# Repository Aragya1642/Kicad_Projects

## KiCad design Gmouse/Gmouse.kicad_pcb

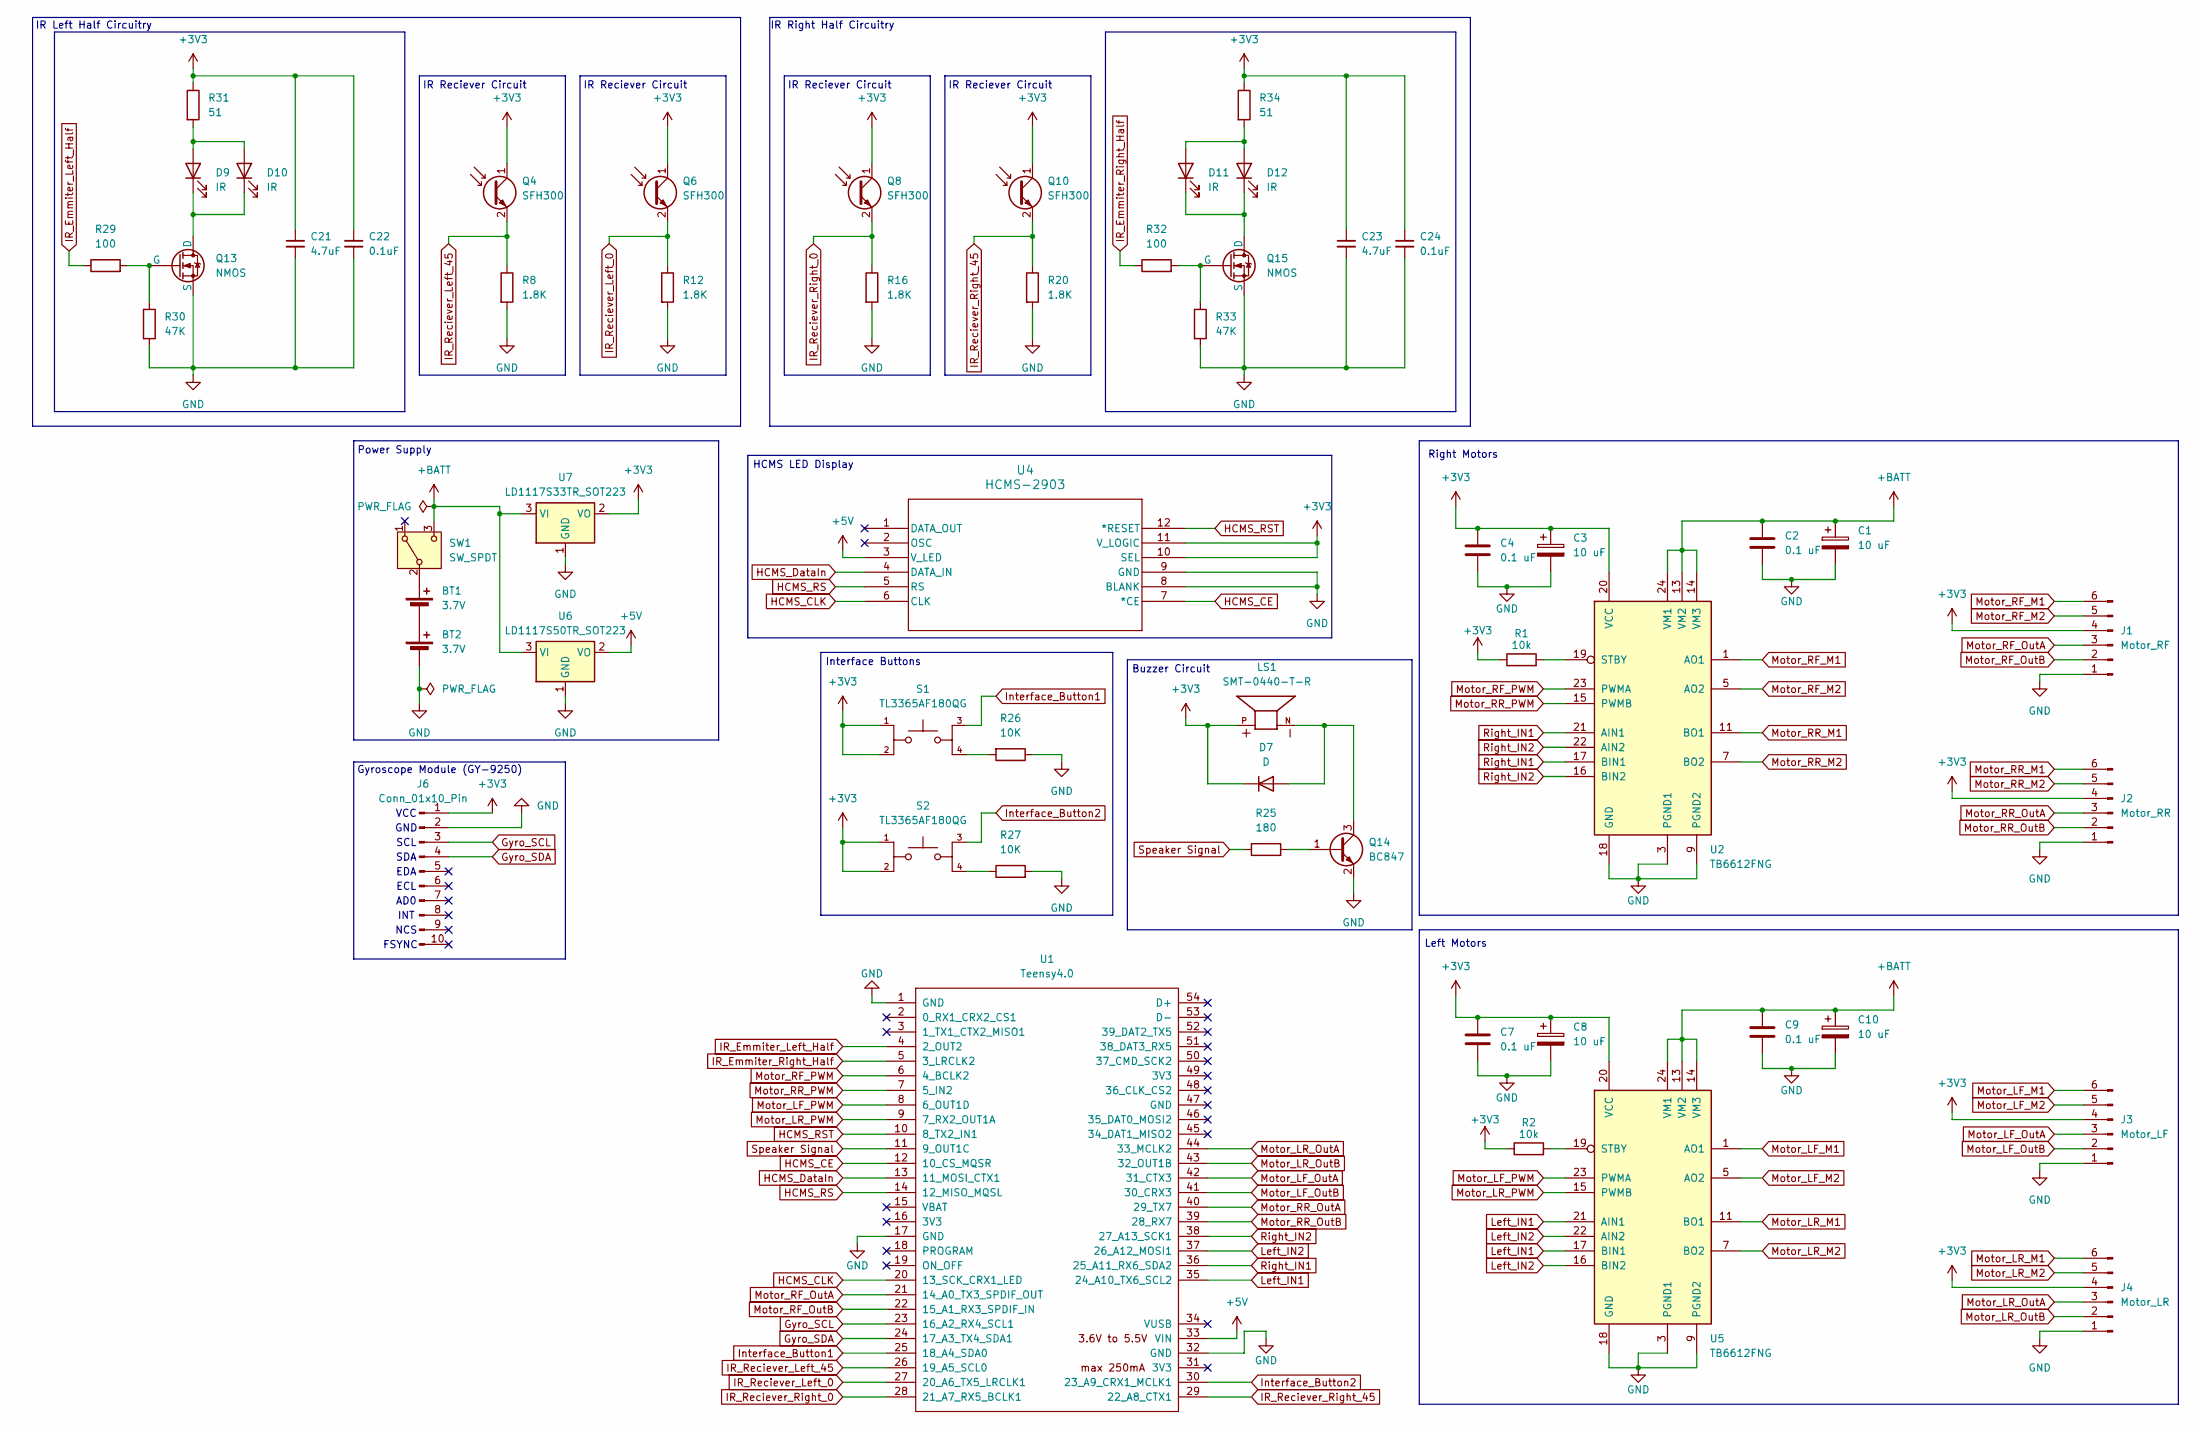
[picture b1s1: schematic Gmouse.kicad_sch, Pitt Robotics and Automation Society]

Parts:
BT1, BT2: 3.7V; JST_PH_B2B-PH-K_1x02_P2.00mm_Vertical
C1, C3, C8, C10: 10 uF; CP_Elec_4x5.4
C2, C4, C7, C9: 0.1 uF; C_1206_3216Metric_Pad1.33x1.80mm_HandSolder
C21, C23: 4.7uF; C_1206_3216Metric_Pad1.33x1.80mm_HandSolder
C22, C24: 0.1uF; C_1206_3216Metric_Pad1.33x1.80mm_HandSolder
D7: D; D_SOD-323_HandSoldering
D9, D10, D11, D12: IR; LED_D5.0mm_Horizontal_O3.81mm_Z9.0mm
J1: Motor_RF; JST_SH_BM06B-SRSS-TB_1x06-1MP_P1.00mm_Vertical
J2: Motor_RR; JST_SH_BM06B-SRSS-TB_1x06-1MP_P1.00mm_Vertical
J3: Motor_LF; JST_SH_BM06B-SRSS-TB_1x06-1MP_P1.00mm_Vertical
J4: Motor_LR; JST_SH_BM06B-SRSS-TB_1x06-1MP_P1.00mm_Vertical
J6: Conn_01x10_Pin; PinHeader_1x10_P2.54mm_Vertical
LS1: SMT-0440-T-R; XDCR_SMT-0440-T-R; PARTREV A
Q4, Q6, Q8, Q10: SFH300; LED_D5.0mm_Horizontal_O1.27mm_Z3.0mm_IRGrey
Q13, Q15: NMOS; SOT-23
Q14: BC847; SOT-23
R1, R2: 10k
R8, R12, R16, R20: 1.8K; R_1206_3216Metric_Pad1.30x1.75mm_HandSolder
R25: 180; R_1206_3216Metric_Pad1.30x1.75mm_HandSolder
R26, R27: 10K; R_1206_3216Metric_Pad1.30x1.75mm_HandSolder
R29, R32: 100; R_1206_3216Metric_Pad1.30x1.75mm_HandSolder
R30, R33: 47K; R_1206_3216Metric_Pad1.30x1.75mm_HandSolder
R31, R34: 51; R_1206_3216Metric_Pad1.30x1.75mm_HandSolder
S1, S2: TL3365AF180QG; SW_TL3365AF180QG; PARTREV A
SW1: SW_SPDT; SW_500SSP1S1M6QEA
U1: Teensy4.0; Teensy40_SMT
U2, U5: TB6612FNG; SSOP-24_5.3x8.2mm_P0.65mm
U4: HCMS-2903; DIP12_HCMS-290X-A_BRA
U6: LD1117S50TR_SOT223; SOT-223-3_TabPin2
U7: LD1117S33TR_SOT223; SOT-223-3_TabPin2

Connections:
+3V3: C3.1, C4.1, C7.1, C8.1, C21.1, C22.1, C23.1, C24.1, D7.1 (K), J1.4, J2.4, J3.4, J4.4, J6.1, LS1.P, Q4.1 (C), Q6.1 (C), Q8.1 (C), Q10.1 (C), R1.1, R2.1, R31.1, R34.1, S1.1, S1.2, S2.1, S2.2, U2.20 (VCC), U4.10 (SEL), U4.11 (V_LOGIC), U5.20 (VCC), U7.2 (VO)
+5V: U1.33 (VIN), U4.3 (V_LED), U6.2 (VO)
+BATT: C1.1, C2.1, C9.1, C10.1, SW1.3 (C), U2.13 (VM2), U2.14 (VM3), U2.24 (VM1), U5.13 (VM2), U5.14 (VM3), U5.24 (VM1), U6.3 (VI), U7.3 (VI)
GND: BT2.2 (-), C1.2, C2.2, C3.2, C4.2, C7.2, C8.2, C9.2, C10.2, C21.2, C22.2, C23.2, C24.2, J1.1, J2.1, J3.1, J4.1, J6.2, Q13.2 (S), Q14.2 (E), Q15.2 (S), R8.2, R12.2, R16.2, R20.2, R26.1, R27.2, R30.2, R33.2, U1.1 (GND), U1.17 (GND), U1.32 (GND), U2.3 (PGND1), U2.4 (PGND1), U2.9 (PGND2), U2.10 (PGND2), U2.18 (GND), U4.8 (BLANK), U4.9 (GND), U5.3 (PGND1), U5.4 (PGND1), U5.9 (PGND2), U5.10 (PGND2), U5.18 (GND), U6.1 (GND), U7.1 (GND)
Gyro_SCL: J6.3, U1.23 (16_A2_RX4_SCL1)
Gyro_SDA: J6.4, U1.24 (17_A3_TX4_SDA1)
HCMS_CE: U1.12 (10_CS_MQSR), U4.7 (*CE)
HCMS_CLK: U1.20 (13_SCK_CRX1_LED), U4.6 (CLK)
HCMS_DataIn: U1.13 (11_MOSI_CTX1), U4.4 (DATA_IN)
HCMS_RS: U1.14 (12_MISO_MQSL), U4.5 (RS)
HCMS_RST: U1.10 (8_TX2_IN1), U4.12 (*RESET)
IR_Emmiter_Left_Half: R29.1, U1.4 (2_OUT2)
IR_Emmiter_Right_Half: R32.1, U1.5 (3_LRCLK2)
IR_Reciever_Left_0: Q6.2 (E), R12.1, U1.27 (20_A6_TX5_LRCLK1)
IR_Reciever_Left_45: Q4.2 (E), R8.1, U1.26 (19_A5_SCL0)
IR_Reciever_Right_0: Q8.2 (E), R16.1, U1.28 (21_A7_RX5_BCLK1)
IR_Reciever_Right_45: Q10.2 (E), R20.1, U1.29 (22_A8_CTX1)
Interface_Button1: S1.3, U1.25 (18_A4_SDA0)
Interface_Button2: S2.3, U1.30 (23_A9_CRX1_MCLK1)
Left_IN1: U1.35 (24_A10_TX6_SCL2), U5.17 (BIN1), U5.21 (AIN1)
Left_IN2: U1.37 (26_A12_MOSI1), U5.16 (BIN2), U5.22 (AIN2)
Motor_LF_M1: J3.6, U5.1 (AO1), U5.2 (AO1)
Motor_LF_M2: J3.5, U5.5 (AO2), U5.6 (AO2)
Motor_LF_OutA: J3.3, U1.42 (31_CTX3)
Motor_LF_OutB: J3.2, U1.41 (30_CRX3)
Motor_LF_PWM: U1.8 (6_OUT1D), U5.23 (PWMA)
Motor_LR_M1: J4.6, U5.11 (BO1), U5.12 (BO1)
Motor_LR_M2: J4.5, U5.7 (BO2), U5.8 (BO2)
Motor_LR_OutA: J4.3, U1.44 (33_MCLK2)
Motor_LR_OutB: J4.2, U1.43 (32_OUT1B)
Motor_LR_PWM: U1.9 (7_RX2_OUT1A), U5.15 (PWMB)
Motor_RF_M1: J1.6, U2.1 (AO1), U2.2 (AO1)
Motor_RF_M2: J1.5, U2.5 (AO2), U2.6 (AO2)
Motor_RF_OutA: J1.3, U1.21 (14_A0_TX3_SPDIF_OUT)
Motor_RF_OutB: J1.2, U1.22 (15_A1_RX3_SPDIF_IN)
Motor_RF_PWM: U1.6 (4_BCLK2), U2.23 (PWMA)
Motor_RR_M1: J2.6, U2.11 (BO1), U2.12 (BO1)
Motor_RR_M2: J2.5, U2.7 (BO2), U2.8 (BO2)
Motor_RR_OutA: J2.3, U1.40 (29_TX7)
Motor_RR_OutB: J2.2, U1.39 (28_RX7)
Motor_RR_PWM: U1.7 (5_IN2), U2.15 (PWMB)
unnamed: BT1.1 (+), SW1.2 (B)
unnamed: BT1.2 (-), BT2.1 (+)
unnamed: D7.2 (A), LS1.N, Q14.3 (C)
unnamed: D9.2 (A), D10.2 (A), R31.2
unnamed: D9.1 (K), D10.1 (K), Q13.3 (D)
unnamed: D11.2 (A), D12.2 (A), R34.2
unnamed: D11.1 (K), D12.1 (K), Q15.3 (D)
unnamed: Q13.1 (G), R29.2, R30.1
unnamed: Q14.1 (B), R25.2
unnamed: Q15.1 (G), R32.2, R33.1
unnamed: R1.2, U2.19 (STBY)
unnamed: R2.2, U5.19 (STBY)
unnamed: R26.2, S1.4
unnamed: R27.1, S2.4
Right_IN1: U1.36 (25_A11_RX6_SDA2), U2.17 (BIN1), U2.21 (AIN1)
Right_IN2: U1.38 (27_A13_SCK1), U2.16 (BIN2), U2.22 (AIN2)
Speaker Signal: R25.1, U1.11 (9_OUT1C)

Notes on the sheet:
Left Motors
Right Motors
EDA
Power Supply
Buzzer Circuit
ECL
GND
NCS
VCC
IR Left Half Circuitry
SDA
FSYNC
INT
IR Right Half Circuitry
HCMS LED Display
IR Reciever Circuit
Gyroscope Module (GY-9250)
Interface Buttons
AD0
SCL

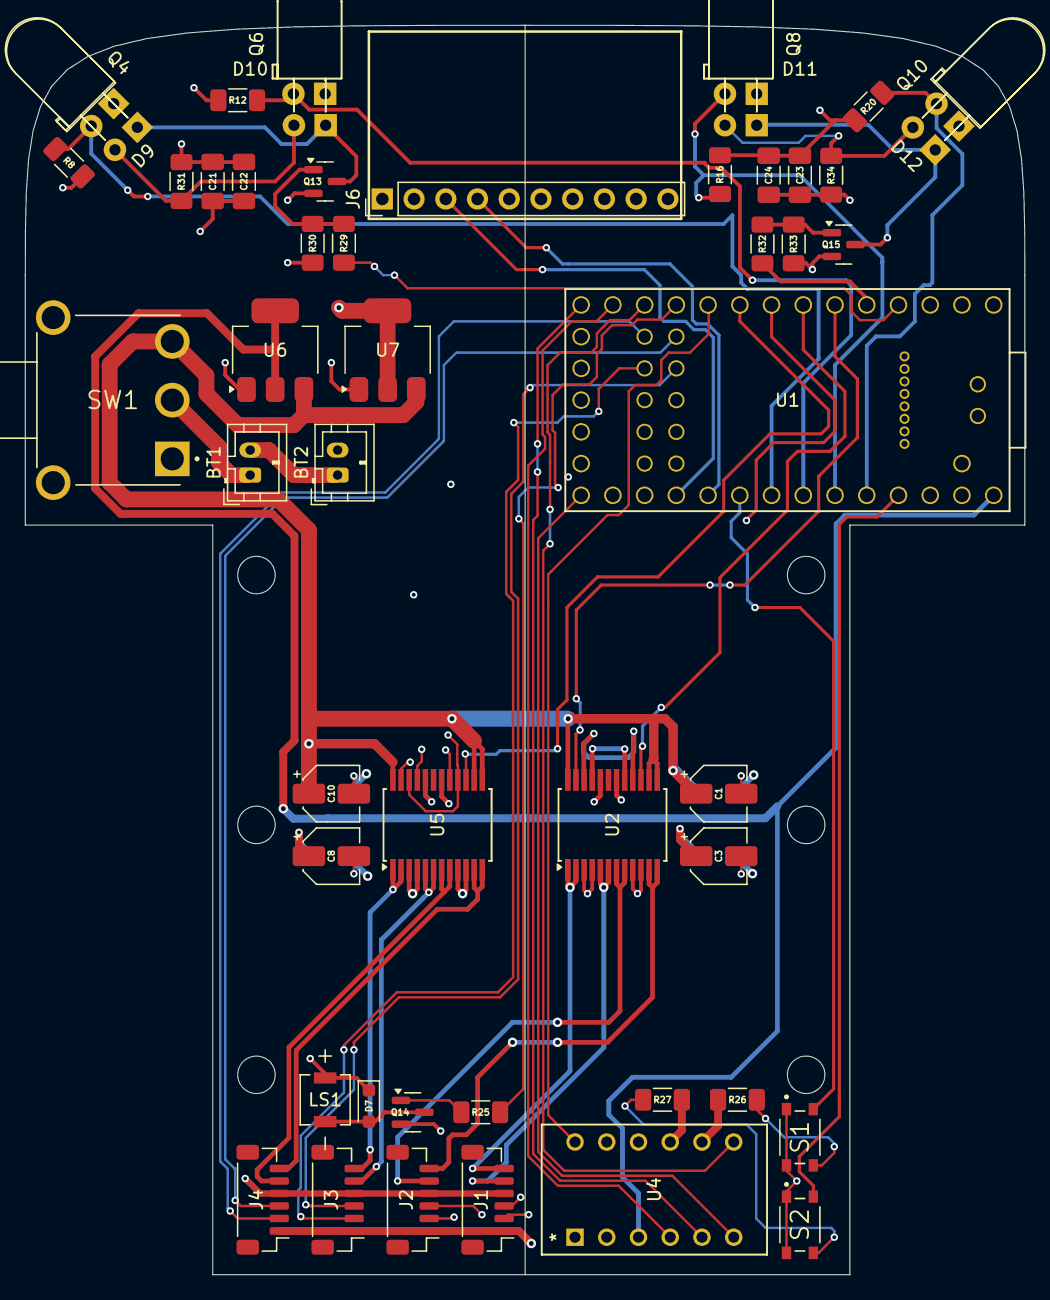
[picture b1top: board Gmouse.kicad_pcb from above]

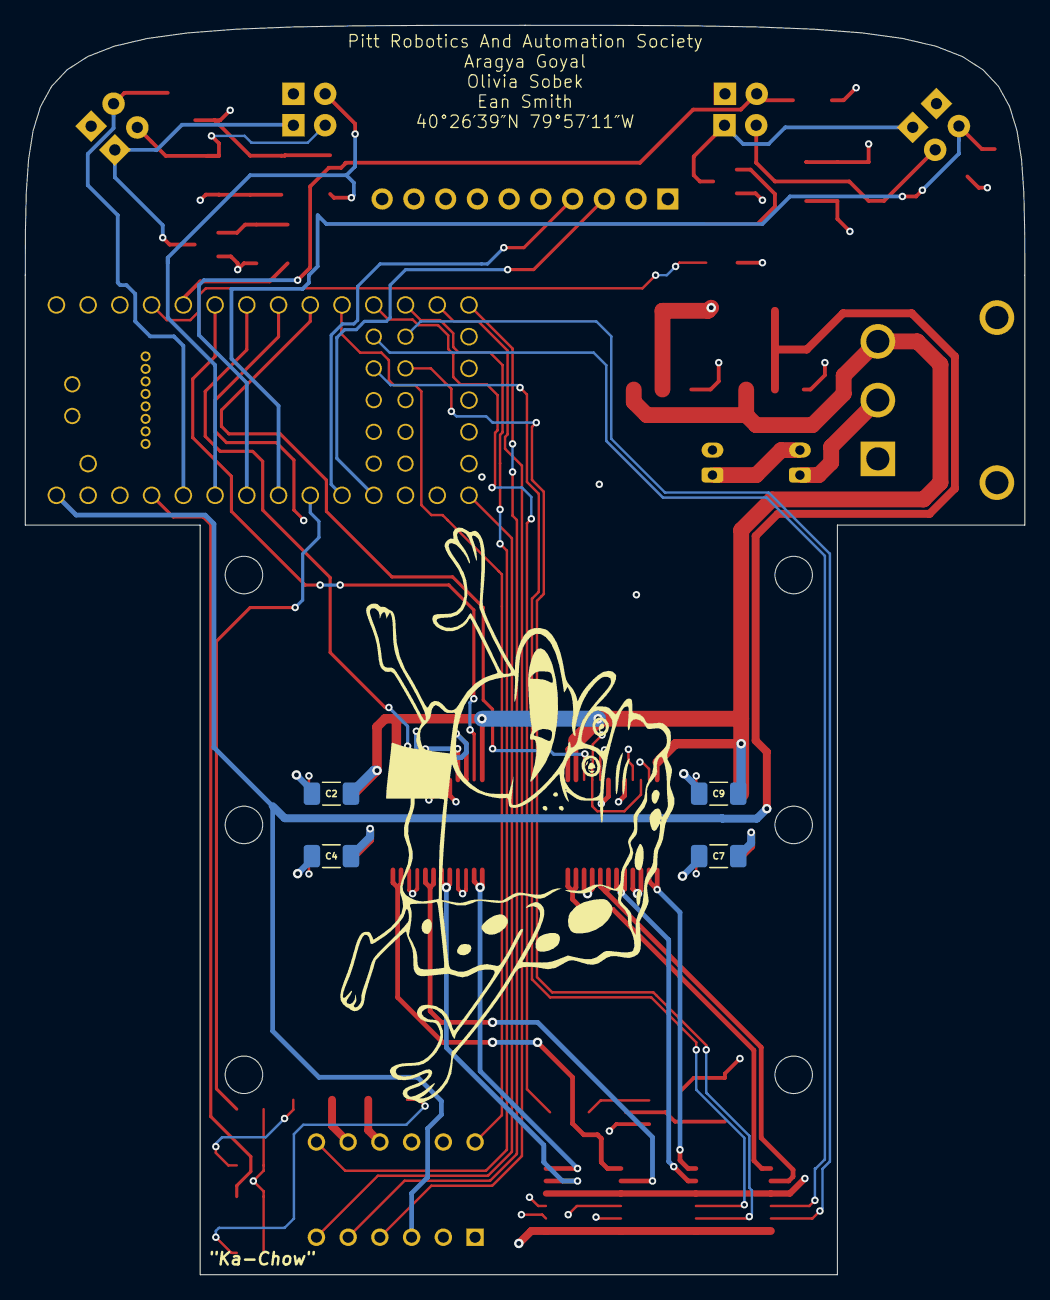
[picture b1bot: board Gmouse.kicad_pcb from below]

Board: 4 copper layers, 80.0 x 100.0 mm, 54 parts (4 on the bottom side), 56 nets.

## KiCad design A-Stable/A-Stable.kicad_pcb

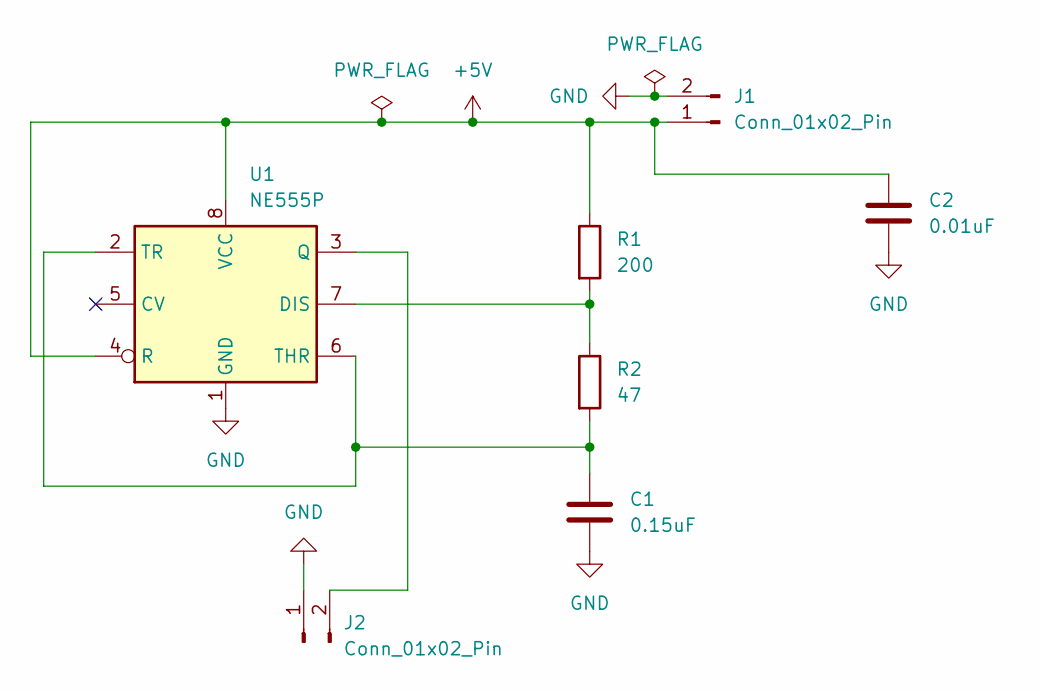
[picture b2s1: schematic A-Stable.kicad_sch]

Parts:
C1: 0.15uF; CP_Radial_D5.0mm_P2.00mm
C2: 0.01uF; C_Disc_D3.8mm_W2.6mm_P2.50mm
J1, J2: Conn_01x02_Pin; PinHeader_2x01_P2.54mm_Vertical
R1: 200; R_Axial_DIN0204_L3.6mm_D1.6mm_P5.08mm_Horizontal
R2: 47; R_Axial_DIN0204_L3.6mm_D1.6mm_P5.08mm_Horizontal
U1: NE555P; DIP-8_W7.62mm

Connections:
+5V: C2.1, J1.1, R1.1, U1.4 (R), U1.8 (VCC)
GND: C1.2, C2.2, J1.2, J2.1, U1.1 (GND)
unnamed: J2.2, U1.3 (Q)
unnamed: R1.2, R2.1, U1.7 (DIS)
unnamed: C1.1, R2.2, U1.2 (TR), U1.6 (THR)

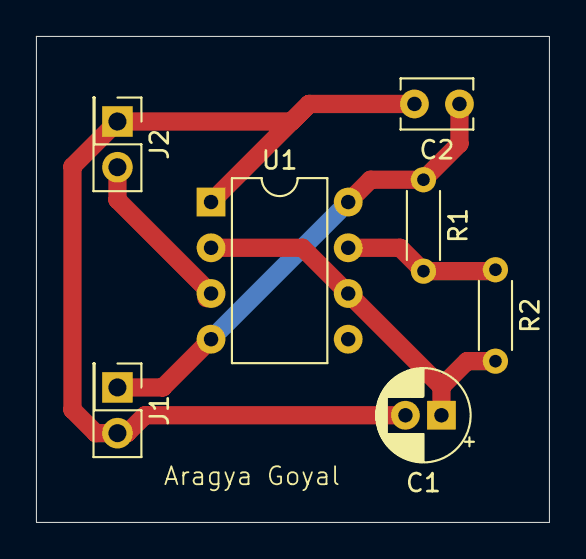
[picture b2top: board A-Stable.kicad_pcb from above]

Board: 2 copper layers, 28.5 x 27.0 mm, 7 parts (0 on the bottom side), 5 nets.

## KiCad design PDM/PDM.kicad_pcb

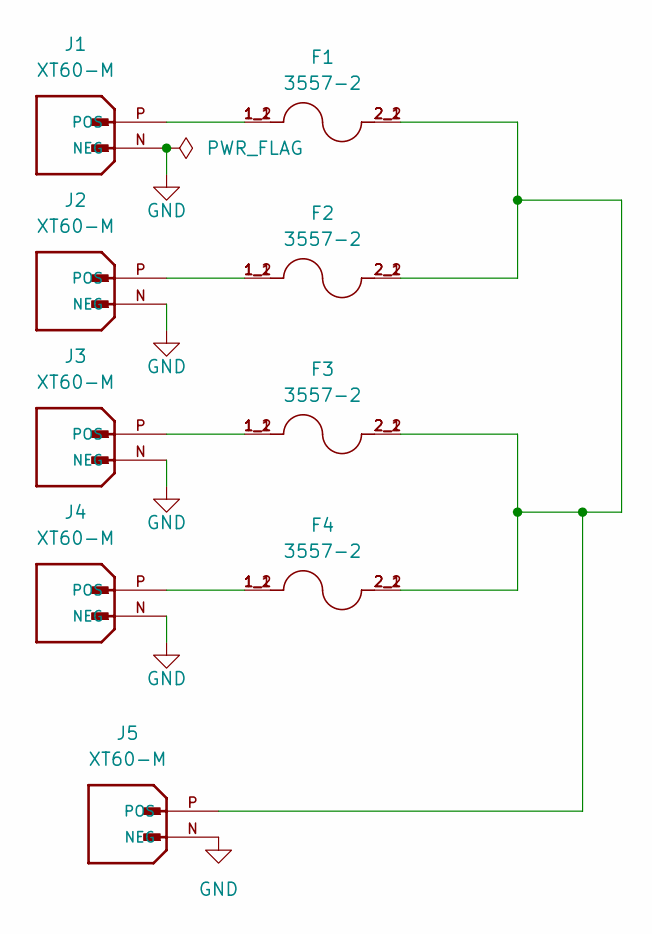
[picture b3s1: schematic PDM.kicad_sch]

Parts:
F1, F2, F3, F4: 3557-2; FUSE_3557-2; PARTREV D
J1, J2, J3, J4, J5: XT60-M; AMASS_XT60-M; PARTREV V1.2

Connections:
GND: J1.N (NEG), J2.N (NEG), J3.N (NEG), J4.N (NEG), J5.N (NEG)
unnamed: F1.1_1, F1.1_2, J1.P (POS)
unnamed: F2.1_1, F2.1_2, J2.P (POS)
unnamed: F3.1_1, F3.1_2, J3.P (POS)
unnamed: F4.1_1, F4.1_2, J4.P (POS)
unnamed: F1.2_1, F1.2_2, F2.2_1, F2.2_2, F3.2_1, F3.2_2, F4.2_1, F4.2_2, J5.P (POS)

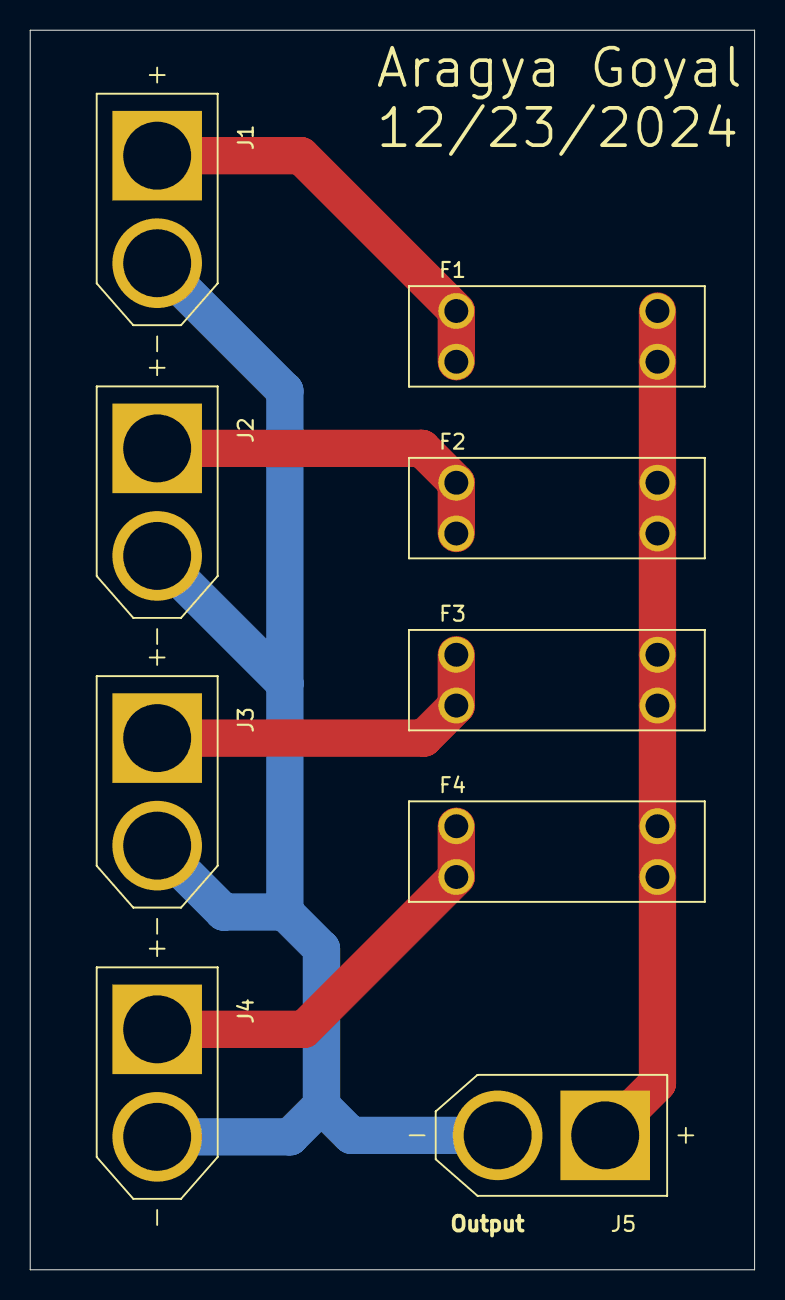
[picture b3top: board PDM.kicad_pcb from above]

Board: 2 copper layers, 48.5 x 83.0 mm, 9 parts (0 on the bottom side), 6 nets.

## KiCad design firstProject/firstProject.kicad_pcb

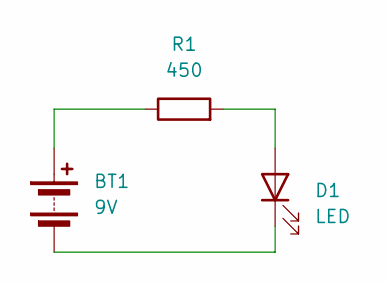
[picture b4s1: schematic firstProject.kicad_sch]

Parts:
BT1: 9V; PinHeader_2x01_P2.54mm_Vertical
D1: LED; LED_D5.0mm
R1: 450; R_Axial_DIN0207_L6.3mm_D2.5mm_P15.24mm_Horizontal

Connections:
unnamed: BT1.1 (+), R1.1
unnamed: BT1.2 (-), D1.1 (K)
unnamed: D1.2 (A), R1.2

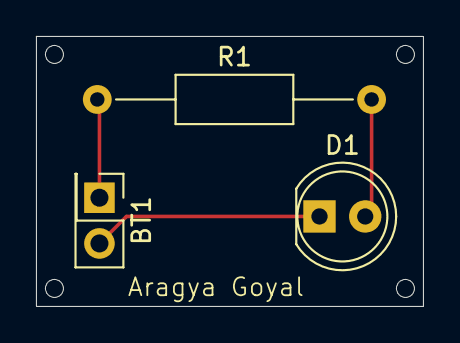
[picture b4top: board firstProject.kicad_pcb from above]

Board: 2 copper layers, 21.5 x 15.0 mm, 3 parts (0 on the bottom side), 3 nets.

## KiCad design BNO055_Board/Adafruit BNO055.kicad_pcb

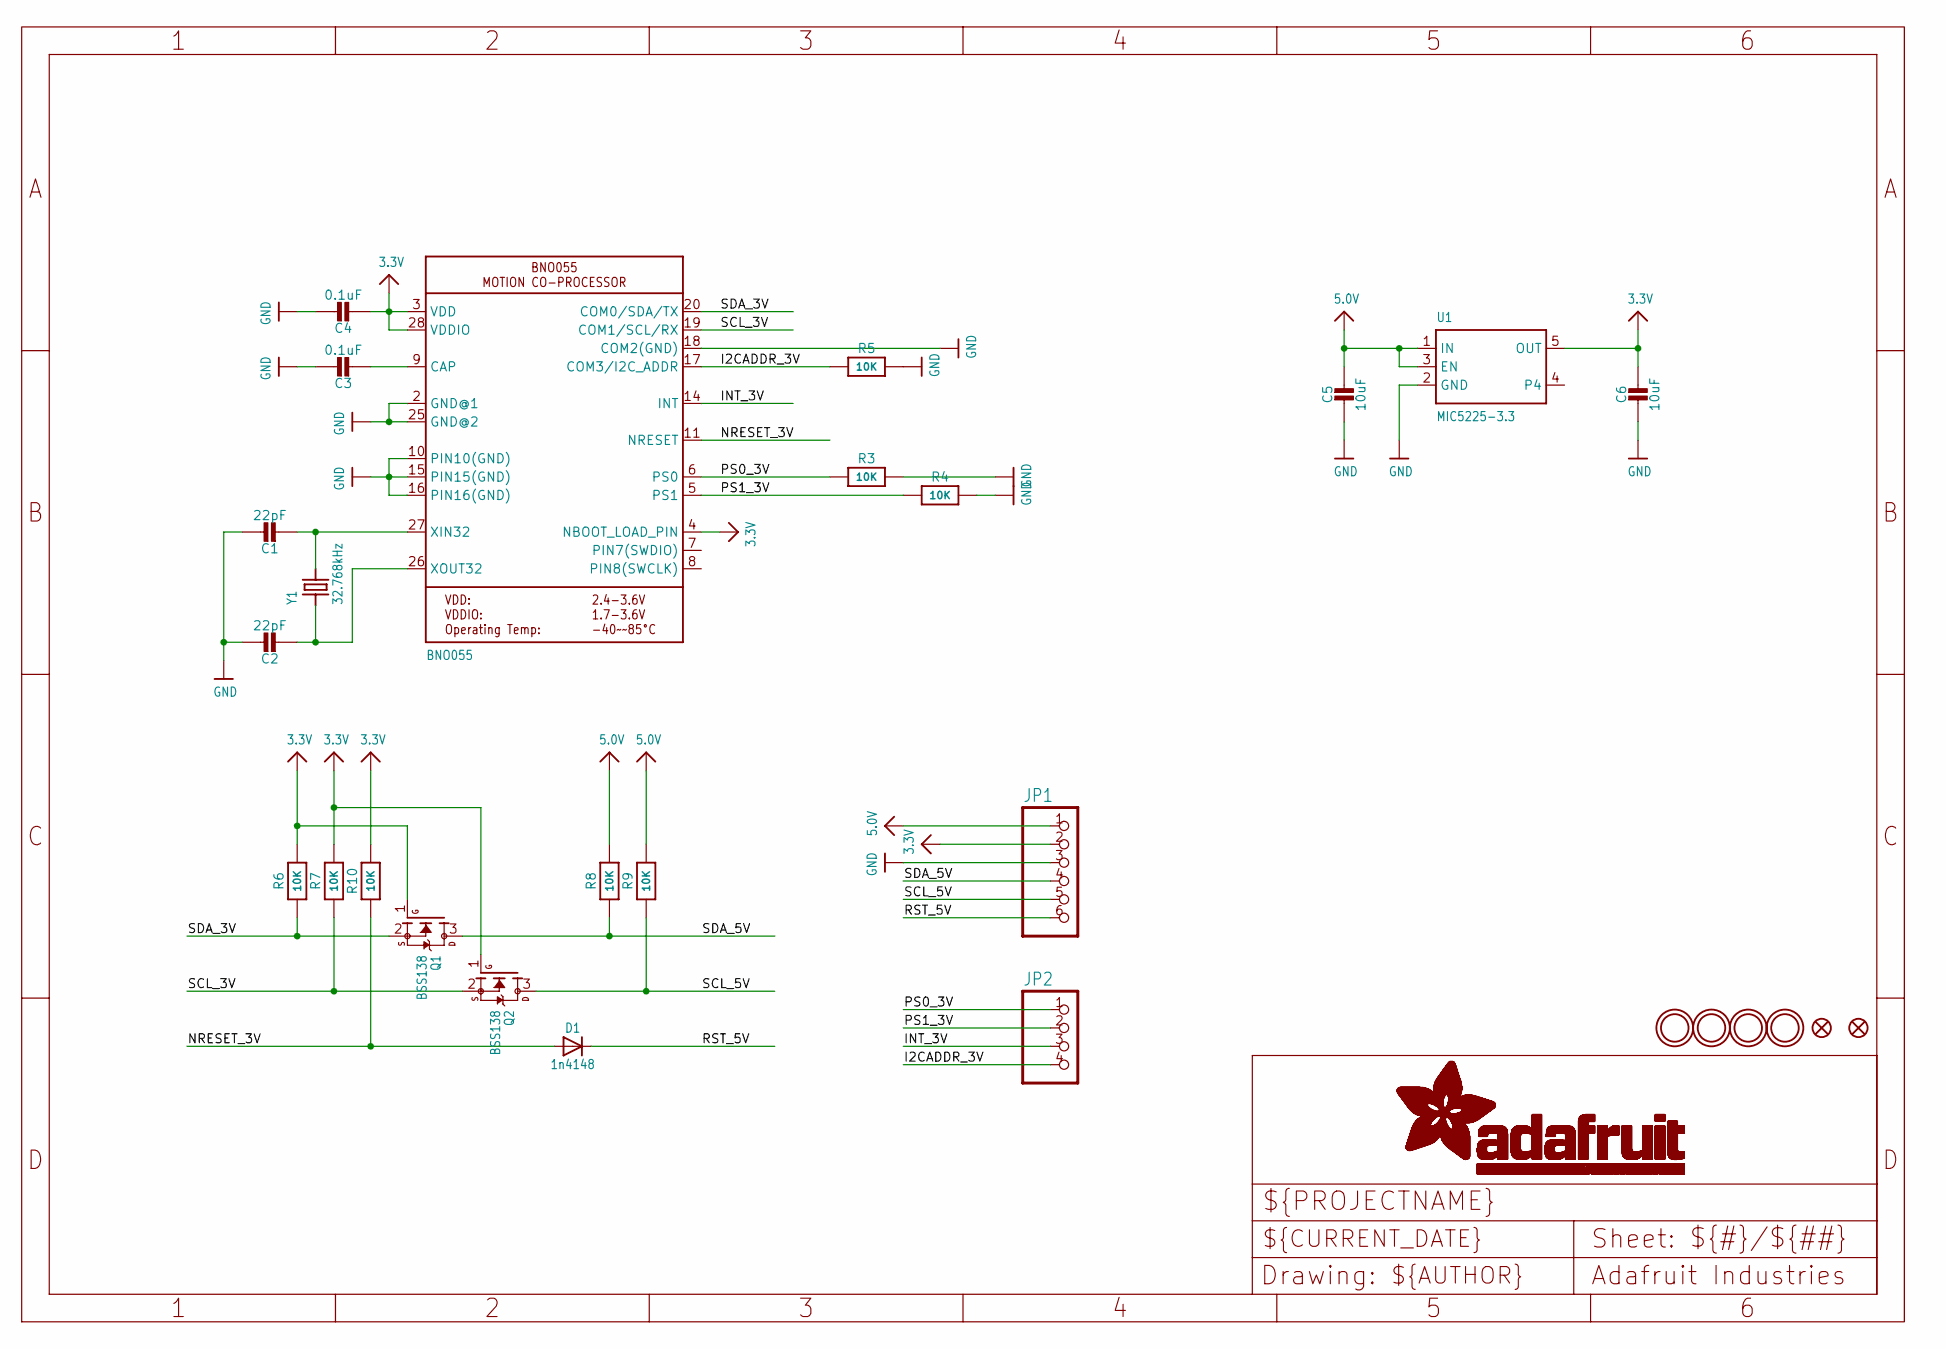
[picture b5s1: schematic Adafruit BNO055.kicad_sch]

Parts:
C1, C2: 22pF; 0805-NO
C3: 0.1uF; 0805-NO
C4: 0.1uF; 0805_10MGAP
C5: 10uF; 0805-NO
C6: 10uF; 0805_10MGAP
D1: 1n4148; SOD-323
FID1, FID2: FIDUCIAL""; FIDUCIAL_1MM
JP1: HEADER-1X676MIL; 1X06_ROUND_76
JP2: HEADER-1X476MIL; 1X04_ROUND_76
Q1, Q2: BSS138; SOT23-WIDE
R3, R4, R5, R6, R7, R10: 10K; 0805-NO
R8, R9: 10K; _0805MP
U1: MIC5225-3.3; SOT23-5
U$2: BNO055
U$29, U$30, U$31, U$32: MOUNTINGHOLE2.5_THICK; MOUNTINGHOLE_2.5_PLATED_THICK
Y1: 32.768kHz; CRYSTAL_8X3.8

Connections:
3.3V: C4.2, C6.1, JP1.2, Q1.1 (G), Q2.1 (G), R6.2, R7.2, R10.2, U1.5 (OUT), U$2.3 (VDD), U$2.4 (NBOOT_LOAD_PIN), U$2.28 (VDDIO)
5.0V: C5.1, JP1.1, R8.2, R9.2, U1.1 (IN), U1.3 (EN)
GND: C1.1, C2.1, C3.1, C4.1, C5.2, C6.2, JP1.3, R3.2, R4.2, R5.2, U1.2 (GND), U$2.2 (GND@1), U$2.10 (PIN10(GND)), U$2.15 (PIN15(GND)), U$2.16 (PIN16(GND)), U$2.18 (COM2(GND)), U$2.25 (GND@2)
I2CADDR_3V: JP2.4, R5.1, U$2.17 (COM3/I2C_ADDR)
INT_3V: JP2.3, U$2.14 (INT)
unnamed: C1.2, U$2.27 (XIN32), Y1.P$4 (2)
unnamed: C2.2, U$2.26 (XOUT32), Y1.P$1 (1)
unnamed: C3.2, U$2.9 (CAP)
NRESET_3V: D1.A, R10.1, U$2.11 (NRESET)
PS0_3V: JP2.1, R3.1, U$2.6 (PS0)
PS1_3V: JP2.2, R4.1, U$2.5 (PS1)
RST_5V: D1.C, JP1.6
SCL_3V: Q2.2 (S), R7.1, U$2.19 (COM1/SCL/RX)
SCL_5V: JP1.5, Q2.3 (D), R9.1
SDA_3V: Q1.2 (S), R6.1, U$2.20 (COM0/SDA/TX)
SDA_5V: JP1.4, Q1.3 (D), R8.1

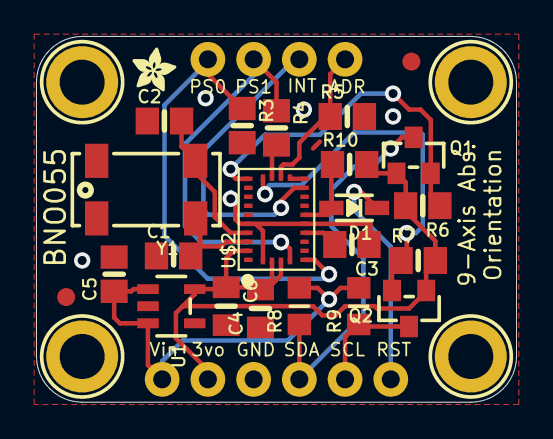
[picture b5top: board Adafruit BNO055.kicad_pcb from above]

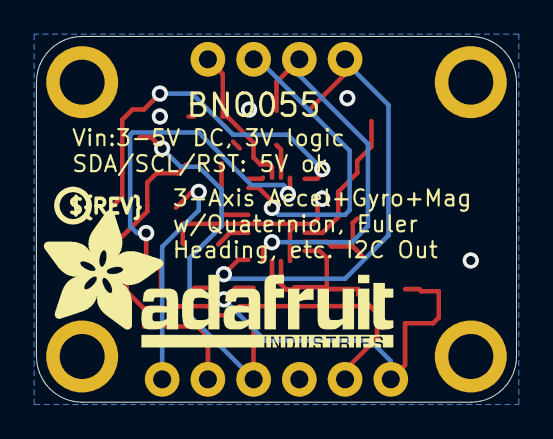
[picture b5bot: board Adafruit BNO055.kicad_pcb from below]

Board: 2 copper layers, 26.7 x 20.3 mm, 31 parts (2 on the bottom side), 16 nets.

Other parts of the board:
U$3: PCBFEAT-REV-040
U$28: ADAFRUIT_TEXT_20MM
U$33: ADAFRUIT_2.5MM

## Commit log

2025-02-21 Added some motors and motor drivers to schematic
2025-02-22 Adds basic motor circuitry and connectors, includes LED Display
2025-02-28 Pushing for desktop
2025-02-28 Added some pins
2025-03-09 Work Done Over Break
2025-03-10 starts pcb design and assigns ton of pins
2025-03-12 cleaned up IR Emitter Circuit
2025-03-12 Started adding traces
2025-03-14 Lot of Manual Routing
2025-03-14 V1 Finished
2025-03-14 Manufacturing Files for V1
2025-03-26 V2 Ready
    Add new gyro board, remove motor stby. add LED Reset
2025-04-23 Most up-to-date Mouse Schematic and Layout
